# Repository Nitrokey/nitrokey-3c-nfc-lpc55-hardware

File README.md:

# Nitrokey 3C NFC Hardware

The hardware files of [Nitrokey 3C NFC](https://shop.nitrokey.com/shop/nk3cn-nitrokey-3c-nfc-148).
The firmware is [here](https://github.com/Nitrokey/nitrokey-3-firmware).

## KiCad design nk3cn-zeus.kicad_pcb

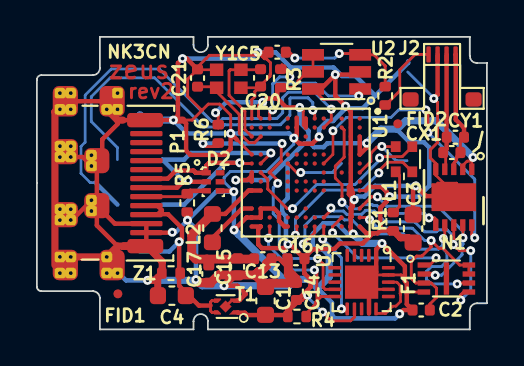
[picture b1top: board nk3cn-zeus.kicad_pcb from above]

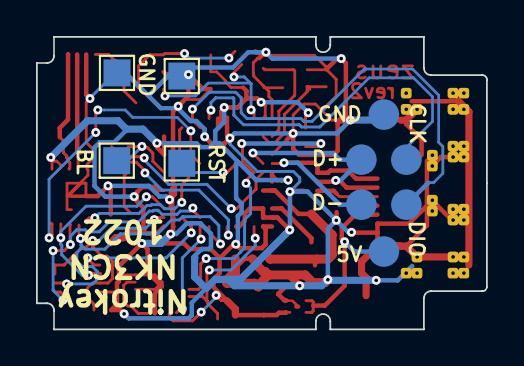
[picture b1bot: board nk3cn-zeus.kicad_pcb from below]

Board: 2 copper layers, 25.0 x 16.2 mm, 40 parts (5 on the bottom side), 33 nets.

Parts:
C1, C3, C4: 22u; C_0603_1608Metric
C2, C14, C15: 100nF; C_0402_1005Metric
C5: 20pF; C_0402_1005Metric
C13, C17: 10uF; C_0402_1005Metric
C16: 47pF; C_0402_1005Metric
C20, C21: 8pF; C_0402_1005Metric
CX1: 100pF; C_0402_1005Metric
CY1: DNP; C_0402_1005Metric
D2: TPD4S012DRYR; UFDFN-6_1.45x1mm
F1: GD25Q16CEIGR; FLASH_2x3_USON8
FID1, FID2: Fiducial; Fiducial_0.5mm_Mask1mm
J2: Conn_01x04; FPC_4_0.5-THD0509-04CL-GF
J3: Conn_01x05; nitro_programming_header
L1: LED_RGBA; RGB_LED_606
L2: 4u7H; L_0603_1608Metric
N1: FM11NC08; DFN-10-1EP_3x3mm_P0.5mm_EP1.55x2.48mm
P1: USB_C_Plug_USB2.0; UTC009-C-vias-optimized
R1: 180R; R_0402_1005Metric
R2: 1k; R_0402_1005Metric
R3, R4, R6: 4.7k; R_0402_1005Metric
R5: 5.1k; R_0402_1005Metric
T1: AP7340-33FS4-7; Diodes_X2-DFN1010_1x1mm_P0.65mm
TP1, TP2, TP3, TP4: TestPoint; TestPoint_Pad_1.5x1.5mm
U1: LPC55S69JEV98K; BGA98C50P13X13_700X700X97N
U2: TTP233D-HA6; TSOT-23-6
U3: SE050; UQFN-20-1EP_3x3mm_P0.4mm_EP1.85x1.85mm
Y1: XRCGB16M000FXN01R0; Crystal-2mmx1.6mm
Z1: GG040205100N2P; R_0402_1005Metric

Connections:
+3V3: C1.1, C3.1, C14.1, C16.1, N1.1, N1.2, R1.1, R3.1, R4.1, R6.1, T1.1, U1.A3, U1.A5, U1.A9, U1.A13, U1.G1, U1.G2, U1.M1, U1.M13, U1.N7, U1.N8, U1.N13, U2.4, U2.5, U3.12
/5V: C4.1, J3.4, P1.A4, P1.B9, T1.3, T1.4, Z1.1
/D+: D2.2, J3.2, P1.A6, U1.M6
/D-: D2.1, J3.3, P1.A7, U1.N6
/NFC+: CX1.1, CY1.1, J2.3, N1.4
/NFC-: CX1.2, CY1.2, J2.4, N1.3
/solo/CAPT: J2.1, R2.1
/solo/FLASH_CS: F1.1, U1.C12
/solo/FLASH_POWER: C2.1, F1.3, F1.7, F1.8, U1.A12
/solo/Sheet5DDC9C58/B: L1.3, U1.H13
/solo/Sheet5DDC9C58/G: L1.2, U1.M7
/solo/Sheet5DDC9C58/NFC_GPIO: N1.10, U1.E6
/solo/Sheet5DDC9C58/R: L1.1, TP2.1, U1.A7
/solo/Sheet5DDC9C58/SENSE1: R3.2, U1.L1, U2.1
/solo/Sheet5DDC9C58/SE_ENA: U1.E13, U3.11
/solo/Sheet5DDC9C58/SIM_RST: R6.2, U1.L7, U3.9
/solo/Sheet5DDC9C58/SIM_VCC: R4.2, U1.L13, U3.10
/solo/Sheet5DDC9C58/SPI_CLK: F1.6, N1.7, U1.F13
/solo/Sheet5DDC9C58/SPI_MISO: F1.2, N1.9, U1.A11
/solo/Sheet5DDC9C58/SPI_MOSI: F1.5, N1.8, U1.E12
/solo/Sheet5DDC9C58/SPI_SS: N1.6, U1.C2
/solo/Sheet5DDC9C58/SWCLK: J3.5, U1.F1
/solo/Sheet5DDC9C58/SWDIO: J3.6, U1.E2
/solo/nRESET: TP1.1, U1.J6
GNDREF: C1.2, C2.2, C3.2, C4.2, C5.2, C13.2, C14.2, C15.2, C16.2, C17.2, C20.1, C21.1, D2.4, F1.4, J2.2, J3.1, N1.5, N1.EXP, P1.A1, P1.B12, P1.S1, R5.2, T1.2, T1.5, TP3.1, TP4.1, U1.B1, U1.B2, U1.B3, U1.B5, U1.B6, U1.B7, U1.B8, U1.B9, U1.B11, U1.B12, U1.B13, U1.H1, U1.H2, U1.J13, U1.M11, U1.M12, U1.N1, U1.N5, U1.N12, U2.2, U2.6, U3.1, U3.14, U3.17, U3.19, U3.21, Y1.3, Z1.2
unnamed: C5.1, R2.2, U2.3
unnamed: C13.1, C15.1, C17.1, L2.2, U1.M9, U1.N9
unnamed: C20.2, U1.N3, Y1.1
unnamed: C21.2, U1.M3, Y1.2
unnamed: D2.3, P1.A5, R5.1
unnamed: L1.4, R1.2
unnamed: L2.1, U1.N11
unnamed: U3.15, U3.18

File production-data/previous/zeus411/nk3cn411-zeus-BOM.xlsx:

BOM VERSION 1 | NK3CN411 – Zeus | BOM Version 1 | NK3CN411 - Zeus | 23.Aug.2022
Component | Description | Part | References | Value | Footprint | Quantity Per PCB | MPN | Manufacturer | Alternative
1 | C0G cap | C | C20 C21 | 8pF | C_0402_1005Metric | 3
2 | C0G cap | C | C16 | 47pF | C_0402_1005Metric | 1
3 | X5R or X7R, 10V | C | C2 C14 C15 | 100n | C_0402_1005Metric | 3
4 | X5R 10V | C | C1 C3 C4 | 22u | C_0603_1608Metric | 3 | C1608X5R1A226M080AC | TDK Corporation
5 | X5R or X7R, 10V | C | C13 C17 | 10uF | C_0402_1005Metric | 2 |  |  | Taiyo Yuden LDK105CBJ106MVLF
6 | C0G cap, pref. 2%, max 5% | C | CX1 | 100pF | C_0402_1005Metric | 1
7 | C0G cap | C | C5 | 20pF | C_0402_1005Metric | 1
8 | Resistor 1% | R | R2 | 1k | R_0402_1005Metric | 1
9 | TVS Diode | tvs diode | D2 | TPD4S012DRYR | UFDFN-6_1.45x1mm | 1 | TPD4S012DRYR | Texas Instruments
10 | SPI flash IC | spi flash | F1 | GD25Q16CEIGR | FLASH_2x3_USON8 | 1 | GD25Q16CEIGR | GigaDevice Semiconductor (HK) Limited
11 | FPC connector 1x4 0.5mm | fpc conn | J2 | Conn_01x04 | FPC_4_0.5-THD0509-04CL-GF | 1 | THD0509-04CL-GF | THD
12 | Inductor | L | L2 | 4u7H | L_0603_1608Metric | 1 | MLF1608A4R7KTA00 | TDK Corporation
13 | RGB LED, red/green/blue/anode | LED_RGBA | L1 | LED_RGBA | RGB_LED_606 | 1 | 150066M153000 | Würth
14 | NFC power harvesting IC | FM11NC08 | N1 | FM11NC08 | MLPD3X3 | 1 | FM11NC08 | Shanghai Fudan Microelectronics Group
15 | USB-C male plug | USB_C_Plug | P1 | UTC-009 | UTC009 | 1 | UTC-009 | Shenzhen Xinda Technology Co., Ltd
16 | Resistor 1% | R | R1 | 180R | R_0402_1005Metric | 1
17 | Resistor 1% | R | R3 R4 R6 | 4.7k | R_0402_1005Metric | 3
18 | 3.3V LDO | TLV742p | T1 | TLV742p | Texas_X2SON-4_1x1mm_P0.65mm | 1 | TLV74233PDQNR | Texas Instruments | Diodes AP7340-33FS4-7
19 | LPC55 microcontroller | LPC55S69JEV98K | U1 | LPC55S69JEV98K | BGA98C50P13X13_700X700X97N | 1 | LPC55S69JEV98K | NXP USA Inc.
20 | Proximity sensor | TTP233D-HA6 | U2 | TTP233 | SOT-23-6 | 1 | TTP233D-HA6 | Tontek Design Tech
21 | Secure element | SE050 | U3 | SE050 | UQFN-20-1EP_3x3mm_P0.4mm_EP1.85x1.85mm | 1 | SE050C1HQ1/Z01SCZ | NXP | SE050C2HQ1/Z01SDZ
22 | Two pin crystal | Crystal | Y1 | XRCGB16M000FXN01R0 | Crystal-2mmx1.6mm | 1 | XRCGB16M000FXN01R0 | Murata
23 | Bidirectional transient-voltage-suppression diode | D_TVS | Z1 | GG040205100N2P | D_0402_1005Metric | 1 | GG040205100N2P | AVX Corporation
24 | Resistor 1% | R | R5 | 5.1k | R_0402_1005Metric | 1
25 | C0G cap | C | CY1 | DNP | C_0402_1005Metric | 0

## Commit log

2026-04-24 nk3cn423
2026-04-24 add LICENSE.txt
2026-04-24 nk3cn424
2026-04-24 add README.md
